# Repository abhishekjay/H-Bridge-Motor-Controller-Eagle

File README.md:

# H-Bridge-Motor-Controller-Eagle
 The repository contains the PCB design schematic and layout of an H Bridge motor controller that I designed on Eagle. 
The file bridge.png provides the schematic of the motor controller. This schematic is drawn in Eagle and mapped onto a PCB, keeping in mind economical and aestheic considerations.
I do not own the image.

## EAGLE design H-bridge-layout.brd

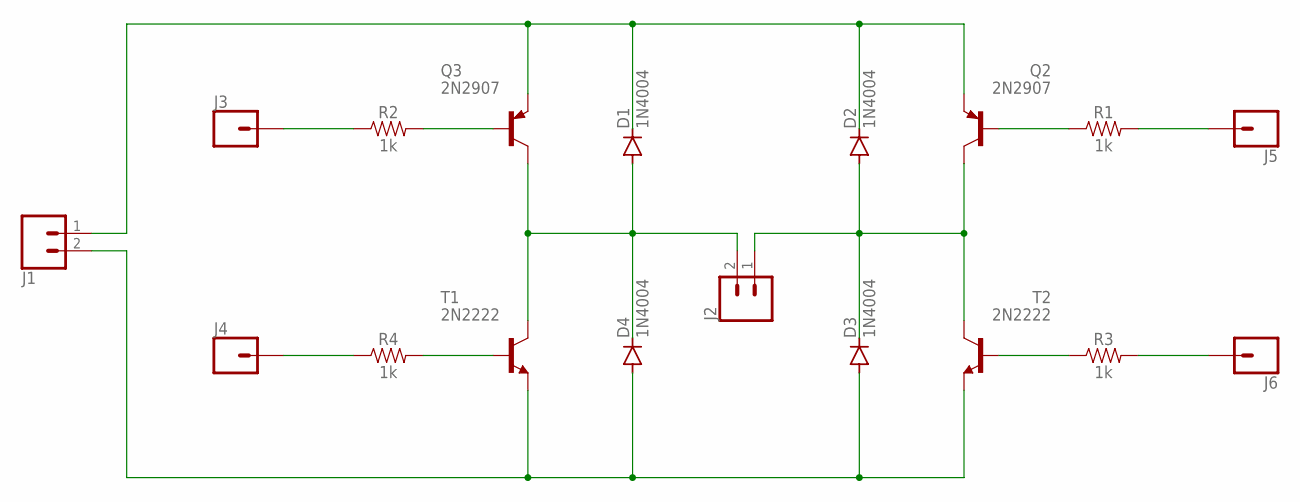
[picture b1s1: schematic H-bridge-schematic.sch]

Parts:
D1, D2, D3, D4: 1N4004; DO41-10
J1, J2: CONN_02; 1X02
J3, J4, J5, J6: CONN_01; 1X01
Q2, Q3: 2N2907; TO18
R1, R2, R3, R4: 1k; AXIAL-0.3
T1, T2: 2N2222; TO18

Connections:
unnamed: D2.A, D3.C, J2.1, Q2.3 (C), T2.3 (C)
unnamed: D3.A, D4.A, J1.2, T1.1 (E), T2.1 (E)
unnamed: D1.A, D4.C, J2.2, Q3.3 (C), T1.3 (C)
unnamed: D1.C, D2.C, J1.1, Q2.1 (E), Q3.1 (E)
unnamed: J3.1, R2.P$1 (1)
unnamed: Q3.2 (B), R2.P$2 (2)
unnamed: J4.1, R4.P$1 (1)
unnamed: R4.P$2 (2), T1.2 (B)
unnamed: Q2.2 (B), R1.P$1 (1)
unnamed: J5.1, R1.P$2 (2)
unnamed: R3.P$1 (1), T2.2 (B)
unnamed: J6.1, R3.P$2 (2)

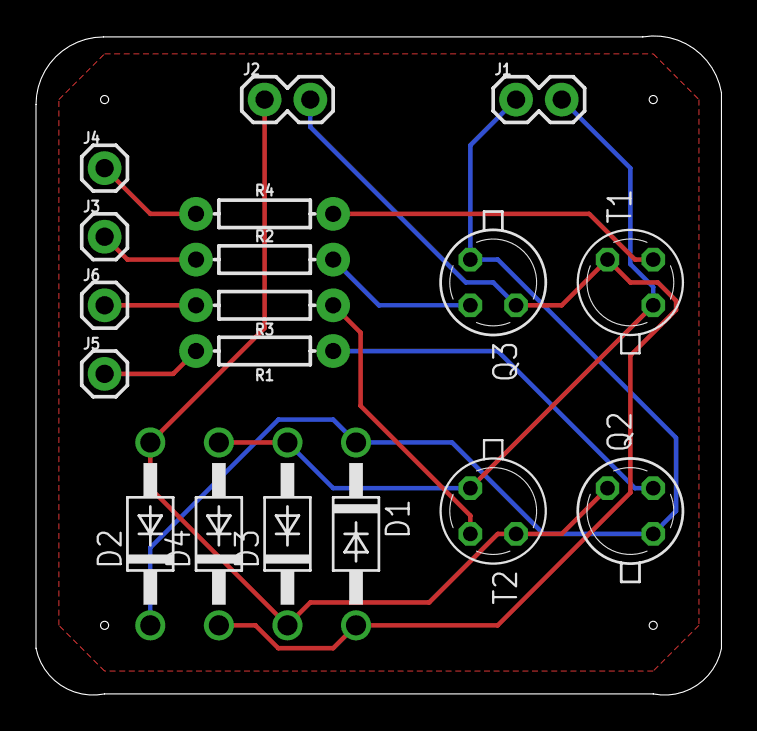
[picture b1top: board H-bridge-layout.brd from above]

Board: 2 copper layers, 38.1 x 36.6 mm, 18 parts (0 on the bottom side), 12 nets.

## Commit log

2021-07-08 Second Commit

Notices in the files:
parts and their libraries:
SparkFun-Connectors: Licensing: Creative Commons ShareAlike 4.0 International - https://creativecommons.org/licenses/by-sa/4.0
